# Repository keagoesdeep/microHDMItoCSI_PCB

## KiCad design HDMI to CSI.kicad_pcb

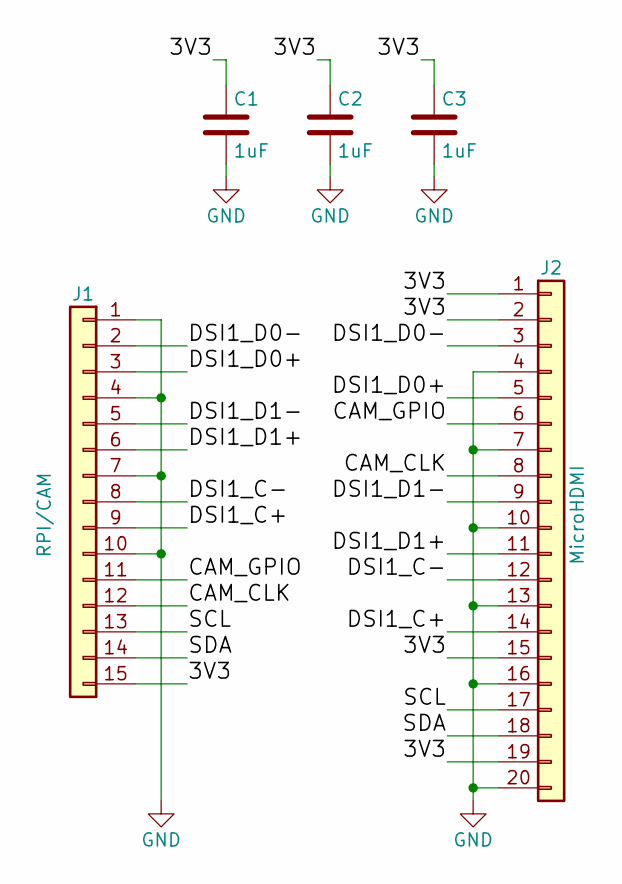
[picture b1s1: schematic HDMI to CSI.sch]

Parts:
C1, C2, C3: 1uF; C_0402
J1: RPI/CAM; TE_1-84952-5_1x15_P1.0mm_Horizontal
J2: MicroHDMI; HDMI_Micro-D_Molex_46765-0x01

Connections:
/3V3: C1.1, C2.1, C3.1, J1.15, J2.1, J2.2, J2.15, J2.19
/CAM_CLK: J1.12, J2.8
/CAM_GPIO: J1.11, J2.6
/DSI1_C+: J1.9, J2.14
/DSI1_C-: J1.8, J2.12
/DSI1_D0+: J1.3, J2.5
/DSI1_D0-: J1.2, J2.3
/DSI1_D1+: J1.6, J2.11
/DSI1_D1-: J1.5, J2.9
/SCL: J1.13, J2.17
/SDA: J1.14, J2.18
GND: C1.2, C2.2, C3.2, J1.1, J1.4, J1.7, J1.10, J2.4, J2.7, J2.10, J2.13, J2.16, J2.20

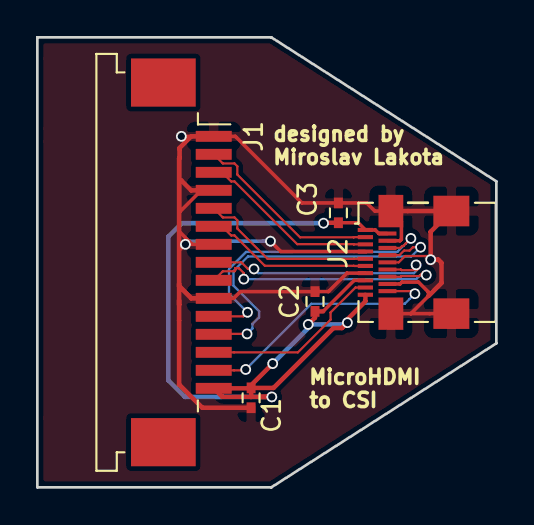
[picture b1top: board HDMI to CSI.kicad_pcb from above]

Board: 2 copper layers, 25.5 x 25.0 mm, 5 parts (0 on the bottom side), 12 nets.

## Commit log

2018-04-07 Schematic ready
2018-04-08 modified Schematic, Cu layers routed
2018-04-08 Finished Silscreen and added Gerber
